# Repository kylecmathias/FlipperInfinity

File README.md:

# Flipper Infinity - Embedded Multi-Protocol Analysis Device

*Ongoing — Hardware complete, PCB designed, firmware in active development*

A handheld multi-protocol signal analysis device built on a custom ESP32 PCB, integrating NFC/RFID, sub-GHz RF, infrared, and WiFi into a single embedded platform with an on-device touchscreen interface.

---

## Hardware

| Module | Protocol | Function |
|---|---|---|
| PN532 | SPI | NFC/RFID read/write/emulate |
| CC1101 | SPI | Sub-GHz RF (433MHz) |
| IR Transmitter | GPIO | Infrared signal transmission |
| IR Receiver | GPIO | Infrared signal capture |
| Arduino Nano ESP32 | — | Main controller, WiFi, promiscuous packet capture |
| ILI9341 TFT Touchscreen | SPI | On-device UI (XPT2046 touch controller) |
| NiMH AA x6 | — | 7.2V battery pack, onboard voltage monitoring |

Custom 2-layer PCB designed in KiCad integrating all modules on a single board with a shared SPI bus, dedicated power rails, and RF-aware layout.

---

## PCB

Designed from scratch in KiCad. Two-layer board with:
- Shared SPI bus (SCK/MOSI/MISO) daisy-chained across TFT, PN532, and CC1101
- Dedicated 1mm VCC and GND power rails
- 100nF decoupling capacitors on all RF modules
- 10µF bulk capacitor on the ESP32 3V3 rail
- Ground pour on both copper layers
- PN532 antenna keepout zone to preserve NFC read range
- CC1101 module positioned at board edge for unobstructed antenna radiation

### Pin Mapping

| Signal | ESP32 Pin | Connected To |
|---|---|---|
| SCK | D13 | TFT, PN532, CC1101 (shared SPI bus) |
| MOSI | D11 | TFT, PN532, CC1101 (shared SPI bus) |
| MISO | D12 | TFT, PN532, CC1101 (shared SPI bus) |
| TFT_SS | A2 | TFT display CS |
| T_SS | A4 | TFT touch CS |
| TFT_RST | D8 | TFT reset |
| DC | D9 | TFT data/command |
| LED | D10 | TFT backlight |
| T_IRQ | D2 | Touch interrupt |
| PN532_SS | A5 | PN532 CS |
| PN532_IRQ | D5 | PN532 interrupt |
| PN532_RST0 | D6 | PN532 reset |
| CC1101_SS | A7 | CC1101 CS |
| CC1101_GDO0 | D3 | CC1101 packet interrupt |
| IR_TX_DAT | D1 | IR transmitter |
| IR_RX_DAT | D0 | IR receiver |
| BATTERY_LVL | A3 | Battery voltage ADC (150k/100k divider) |
| BATTERY_SRC | D7 | USB/battery source detect (10k/20k divider) |
| VIN | VIN | 7.2V NiMH battery pack |

---

## Firmware

Written in C++ using ESP-IDF with FreeRTOS. Each protocol runs as an isolated task, scheduled cooperatively to avoid resource contention across shared buses.

- **Multi-protocol scheduling** — FreeRTOS tasks isolate NFC, RF, IR, and WiFi logic
- **Bus management** — SPI peripherals share the ESP32's interface without conflicts via chip select
- **Touchscreen UI** — LVGL-based interface built with SquareLine Studio for on-device workflow control
- **WiFi** — promiscuous mode packet capture for raw 802.11 frame analysis

---

## Planned Features

### WiFi
Network scanning, packet monitoring, device inventory, deauthentication, file server, MAC spoofing, captive portal, beacon spam

### Bluetooth
BLE device scanner, packet sniffer, device logger

### NFC
Read, write, emulate, sniff — supports Mifare Classic cards

### RFID
Read, write, emulate

### IR
Transmit, receive, universal remote, signal replay

### RF (CC1101)
Frequency analyzer, listen, decode, replay, transmit

---

## Repository Structure

```
FlipperInfinity/
├── include/                # Header files to include (.hpp)
├── src/                    # Firmware source (.cpp, ESP-IDF) and build files (CMakeLists, idf_component)
│   ├── ui/                 # UI files generated with EEZ Studio (.c, .h)
├── hardware/
│   ├── schematic/          # KiCad schematic (.kicad_sch)
│   ├── pcb/                # KiCad PCB layout (.kicad_pcb)
│   └── gerbers/
│       └── v1.0/           # Manufacturing files for JLCPCB
├── partitions.csv          # ESP32s3 partitions
├── sdkconfig.defaults      # Configuration overrides
├── platformio.ini          # Platformio configuration
└── README.md
```

---

## Tech Stack

ESP32 · ESP-IDF · FreeRTOS · LVGL · SquareLine Studio · C++ · SPI · PN532 · CC1101 · KiCad

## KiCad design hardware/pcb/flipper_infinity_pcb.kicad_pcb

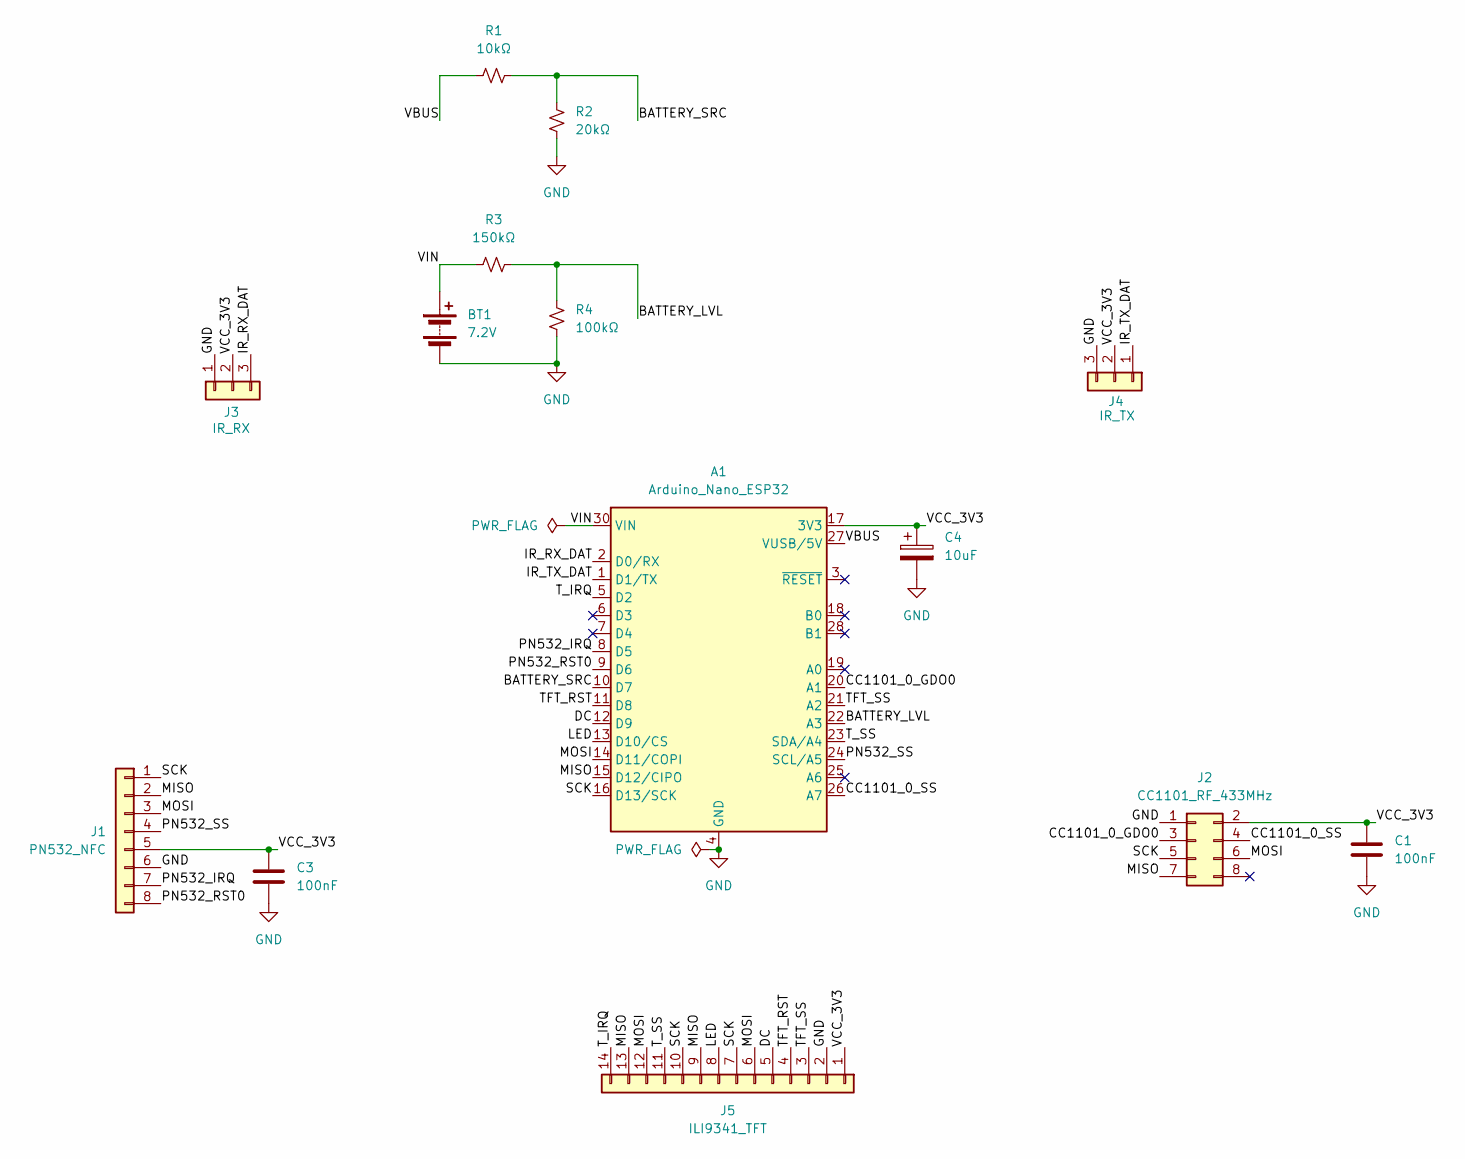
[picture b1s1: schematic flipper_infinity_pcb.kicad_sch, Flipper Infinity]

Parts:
A1: Arduino_Nano_ESP32; Arduino_Nano
BT1: 7.2V; PinHeader_1x02_P2.54mm_Vertical
C1, C3: 100nF; C_0805_2012Metric
C4: 10uF; CP_Radial_D5.0mm_P2.00mm
J1: PN532_NFC; PinHeader_1x08_P2.54mm_Vertical
J2: CC1101_RF_433MHz; PinHeader_2x04_P2.54mm_Vertical
J3: IR_RX; PinHeader_1x03_P2.54mm_Vertical
J4: IR_TX; PinHeader_1x03_P2.54mm_Vertical
J5: ILI9341_TFT; PinHeader_1x14_P2.54mm_Vertical
R1: 10kΩ; R_Axial_DIN0207_L6.3mm_D2.5mm_P10.16mm_Horizontal
R2: 20kΩ; R_Axial_DIN0207_L6.3mm_D2.5mm_P10.16mm_Horizontal
R3: 150kΩ; R_Axial_DIN0207_L6.3mm_D2.5mm_P10.16mm_Horizontal
R4: 100kΩ; R_Axial_DIN0207_L6.3mm_D2.5mm_P10.16mm_Horizontal

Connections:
/BATTERY_LVL: A1.22 (A3), R3.2, R4.2
/BATTERY_SRC: A1.10 (D7), R1.2, R2.1
/CC1101_0_GDO0: A1.20 (A1), J2.3
/CC1101_0_SS: A1.26 (A7), J2.4
/DC: A1.12 (D9), J5.5
/IR_RX_DAT: A1.2 (D0/RX), J3.3
/IR_TX_DAT: A1.1 (D1/TX), J4.1
/LED: A1.13 (D10/CS), J5.8
/MISO: A1.15 (D12/CIPO), J1.2, J2.7, J5.9, J5.13
/MOSI: A1.14 (D11/COPI), J1.3, J2.6, J5.6, J5.12
/PN532_IRQ: A1.8 (D5), J1.7
/PN532_RST0: A1.9 (D6), J1.8
/PN532_SS: A1.24 (SCL/A5), J1.4
/SCK: A1.16 (D13/SCK), J1.1, J2.5, J5.7, J5.10
/TFT_RST: A1.11 (D8), J5.4
/TFT_SS: A1.21 (A2), J5.3
/T_IRQ: A1.5 (D2), J5.14
/T_SS: A1.23 (SDA/A4), J5.11
/VBUS: A1.27 (VUSB/5V), R1.1
/VCC_3V3: A1.17 (3V3), C1.1, C3.1, C4.1, J1.5, J2.2, J3.2, J4.2, J5.1
/VIN: A1.30 (VIN), BT1.1 (+), R3.1
GND: A1.4 (GND), A1.29 (GND), BT1.2 (-), C1.2, C3.2, C4.2, J1.6, J2.1, J3.1, J4.3, J5.2, R2.2, R4.1

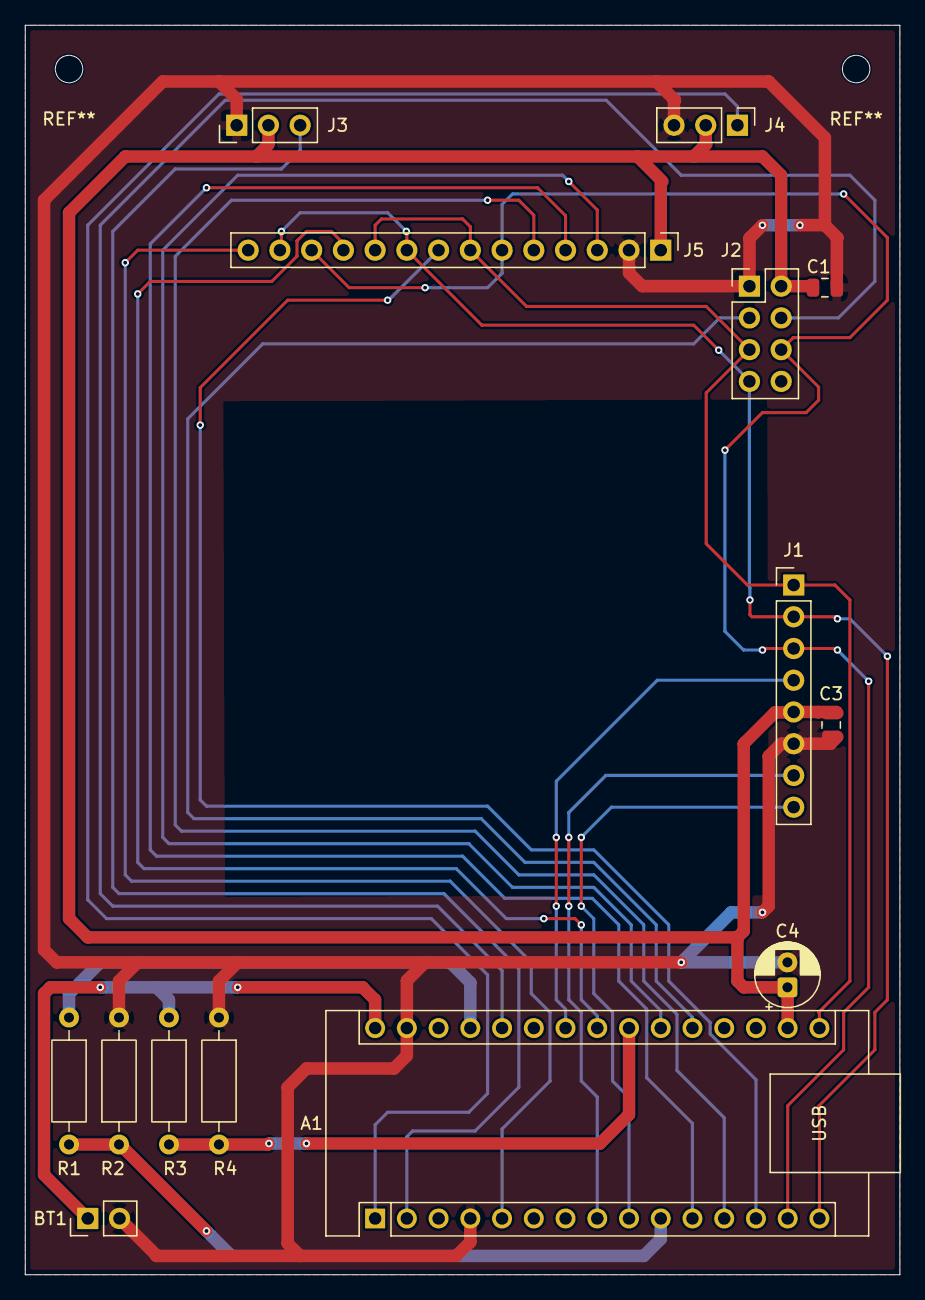
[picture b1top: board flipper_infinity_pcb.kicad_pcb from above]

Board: 2 copper layers, 70.0 x 100.0 mm, 14 parts (0 on the bottom side), 22 nets.

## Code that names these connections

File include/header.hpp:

#pragma once

#include <stdio.h>
#include <sys/stat.h>

#include <string>
#include <atomic>
#include <optional>
#include <array>
#include <format>

#include <freertos/FreeRTOS.h>
#include <freertos/task.h>
#include <freertos/event_groups.h>
#include <freertos/semphr.h>
#include <freertos/queue.h>

#include <driver/spi_master.h>
#include <driver/gpio.h>
#include <esp_littlefs.h>
#include <esp_heap_caps.h>
#include <esp_random.h>
#include <esp_timer.h>
#include <esp_private/periph_ctrl.h>

#include <esp_adc/adc_oneshot.h>
#include <esp_adc/adc_cali.h>
#include <esp_adc/adc_cali_scheme.h>

#include <esp_lcd_panel_io.h>
#include <esp_lcd_panel_vendor.h>
#include <esp_lcd_panel_ops.h>
#include <esp_lcd_ili9341.h>
#include <esp_lcd_touch_xpt2046.h>
#include <esp_lvgl_port.h>

#include <nvs_flash.h>
#include <esp_mac.h>
#include <esp_netif.h>
#include <esp_event.h>
#include <esp_wifi_default.h>
#include <esp_wifi.h>
#include <esp_log.h>
#include <esp_system.h>
#include <esp_netif_net_stack.h>
#include <lwip/sockets.h>
#include <lwip/etharp.h>
#include <lwip/netif.h>
#include <lwip/ip4_addr.h>
#include <mdns.h>

#include <esp_bt.h>
#include <esp_nimble_hci.h>
#include <nimble/nimble_port.h>
#include <nimble/nimble_port_freertos.h>
#include <host/ble_hs.h>
#include <host/ble_gap.h>
#include <host/ble_hs_adv.h>
#include <host/util/util.h>
#include <services/gap/ble_svc_gap.h>
#include <pn532_driver.hpp>

#include <rom/ets_sys.h>

#include <driver/rmt_tx.h>
#include <driver/rmt_rx.h>

#include "helpers.hpp"

inline constexpr const char* LITTLEFS_MOUNT = "/flipperinf";
inline constexpr const char* LITTLEFS_PART_LABEL = "storage";
inline constexpr size_t FILENAME_LEN = 64;
inline constexpr size_t FILEPATH_LEN = 128;

inline constexpr uint8_t HIGH = 1;
inline constexpr uint8_t LOW = 0;

inline constexpr const char* DISPLAY_HOSTNAME = "iPhone";
inline constexpr size_t HOSTNAME_LEN = 32;

inline constexpr size_t LINE_BUFFER_LEN = 128;

inline constexpr spi_host_device_t LCD_HOST = SPI2_HOST;
inline constexpr uint64_t LCD_PIXEL_CLK = (40 * 1000 * 1000);
inline constexpr uint64_t LCD_TOUCH_CLK = (2 * 1000 * 1000);
inline constexpr uint16_t LCD_H_RES = 240;
inline constexpr uint16_t LCD_V_RES = 320;
inline constexpr float LCD_X_MULTIPLIER = 1.00f;
inline constexpr float LCD_Y_MULTIPLIER = 1.00f;
inline constexpr int16_t LCD_X_OFFSET = 0;
inline constexpr int16_t LCD_Y_OFFSET = 15;
inline constexpr uint16_t Y_DRIFT_END = 199;
inline constexpr uint16_t X_DRIFT_START = 320;
inline constexpr uint8_t ADC_SAMPLES = 8;
inline constexpr float V_MAX = 3.3f;
inline constexpr uint8_t ADC_RES = 12;
inline constexpr uint16_t ADC_MAX = (1UL << ADC_RES) - 1;
inline constexpr uint16_t BATT_ADC_MAX = ADC_MAX;
inline constexpr uint16_t BATT_ADC_MIN = 2.4f * ADC_MAX / V_MAX;

inline constexpr size_t MAX_SCAN_NETWORKS = 40;
inline constexpr size_t MAX_INVENTORY_DEVICES = 256;
inline constexpr size_t MAC_STR_LEN = 18;
inline constexpr size_t MANUFACTURER_STR_LEN = 32;
inline constexpr int8_t RSSI_MIN = -100;
inline constexpr int8_t RSSI_MAX = -20;
inline constexpr size_t MAX_UUIDS16 = 4;

inline constexpr spi_host_device_t PN532_HOST = SPI2_HOST;
inline constexpr uint32_t PN532_CLK = 2500000;

namespace GPIO_PINS {
    static constexpr gpio_num_t NONE = GPIO_NUM_NC;

    static constexpr gpio_num_t SCK = GPIO_NUM_48; //D13
    static constexpr gpio_num_t MOSI = GPIO_NUM_38; //D11
    static constexpr gpio_num_t MISO = GPIO_NUM_47; //D12

    static constexpr gpio_num_t TFT_SS = GPIO_NUM_3; //A2
    static constexpr gpio_num_t TFT_DC = GPIO_NUM_18; //D9
    static constexpr gpio_num_t TFT_RST = GPIO_NUM_17; //D8
    static constexpr gpio_num_t TFT_BKL = GPIO_NUM_21; //D10 but rn is on 3V3

    static constexpr gpio_num_t TOUCH_SS = GPIO_NUM_11; //A4
    static constexpr gpio_num_t TOUCH_IRQ = GPIO_NUM_5; //D2
    
    static constexpr gpio_num_t CC1101_SS = GPIO_NUM_14; //A7
    static constexpr gpio_num_t CC1101_GDO0 = GPIO_NUM_6; //A1

    static constexpr gpio_num_t PN532_SS = GPIO_NUM_12; //A5
    static constexpr gpio_num_t PN532_IRQ = GPIO_NUM_8; //D5
    static constexpr gpio_num_t PN532_RST = GPIO_NUM_9; //D6

    static constexpr gpio_num_t IR_RX = GPIO_NUM_44; //D0
    static constexpr gpio_num_t IR_TX = GPIO_NUM_43; //D1

    static constexpr gpio_num_t BATT_SRC = GPIO_NUM_10; //D7
    static constexpr gpio_num_t BATT_LVL = GPIO_NUM_4; //A3
};

inline constexpr uint8_t BATTERY_LEVEL_MIN = 0;
inline constexpr uint8_t BATTERY_LEVEL_MAX = 100;

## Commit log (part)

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2026-05-04 added initial files
2026-05-04 moved files to src folder
2026-05-19 added pcb files
